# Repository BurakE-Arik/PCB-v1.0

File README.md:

# PCB Design v1.0 

## Description
This project is my first practical hardware work as a first-year Computer Engineering student. I developed it to learn hardware design processes, how to read schematics, and the standards used in PCB production.

---

## Visuals
For reviewers to quickly see the design, the front and back views of the board are shown below:

### PCB Front View

### PCB Back View

---

## Technical Details & Tools
Libraries and design rules (DRC) were used during the design process.

* **Design Tool:** Autodesk Eagle v9.6.2
* **Libraries:** * [SparkFun Electronics](https://github.com/sparkfun/SparkFun-Eagle-Libraries) (Connectors, LED, PowerSymbols, Resistors, Sensors, Switches)
    * [Custom Library](Design_Files/Custom_Library/) (Designed for specific componenets Arduiono Nano and LM 35)
* **Design Rules:** To minimize errors in the schematics, checks were performed using the [SparkFun DRU](Design_Files/DRU%20File/) files.

---

## Project Structure
The project folder is organized as follows:

* **[Design_Files](Design_Files):** Source Autodesk EAGLE schematic (.sch) and board (.brd) files.
* **[Gerber](Gerber):** Output files prepared for manufacturing in RS-274X format.
* **[Images](Images):** High-resolution design images.

---

## How to Use
1. `/Design_Files/Schemas` You can open the files in this folder using EAGLE or any compatible CAD software.
2. If you want to manufacture the board, you can directly send the `.zip` file in the `/Gerber` folder to a PCB manufacturer (such as JLCPCB, PCBWay, etc.).

---
**Author:** Burak Eslem Arık
**Contact:** [burakar1912@gmail.com](burakar1912@gmail.com), [Linkedin](https://www.linkedin.com/in/burak-eslem-arik-481045208/)

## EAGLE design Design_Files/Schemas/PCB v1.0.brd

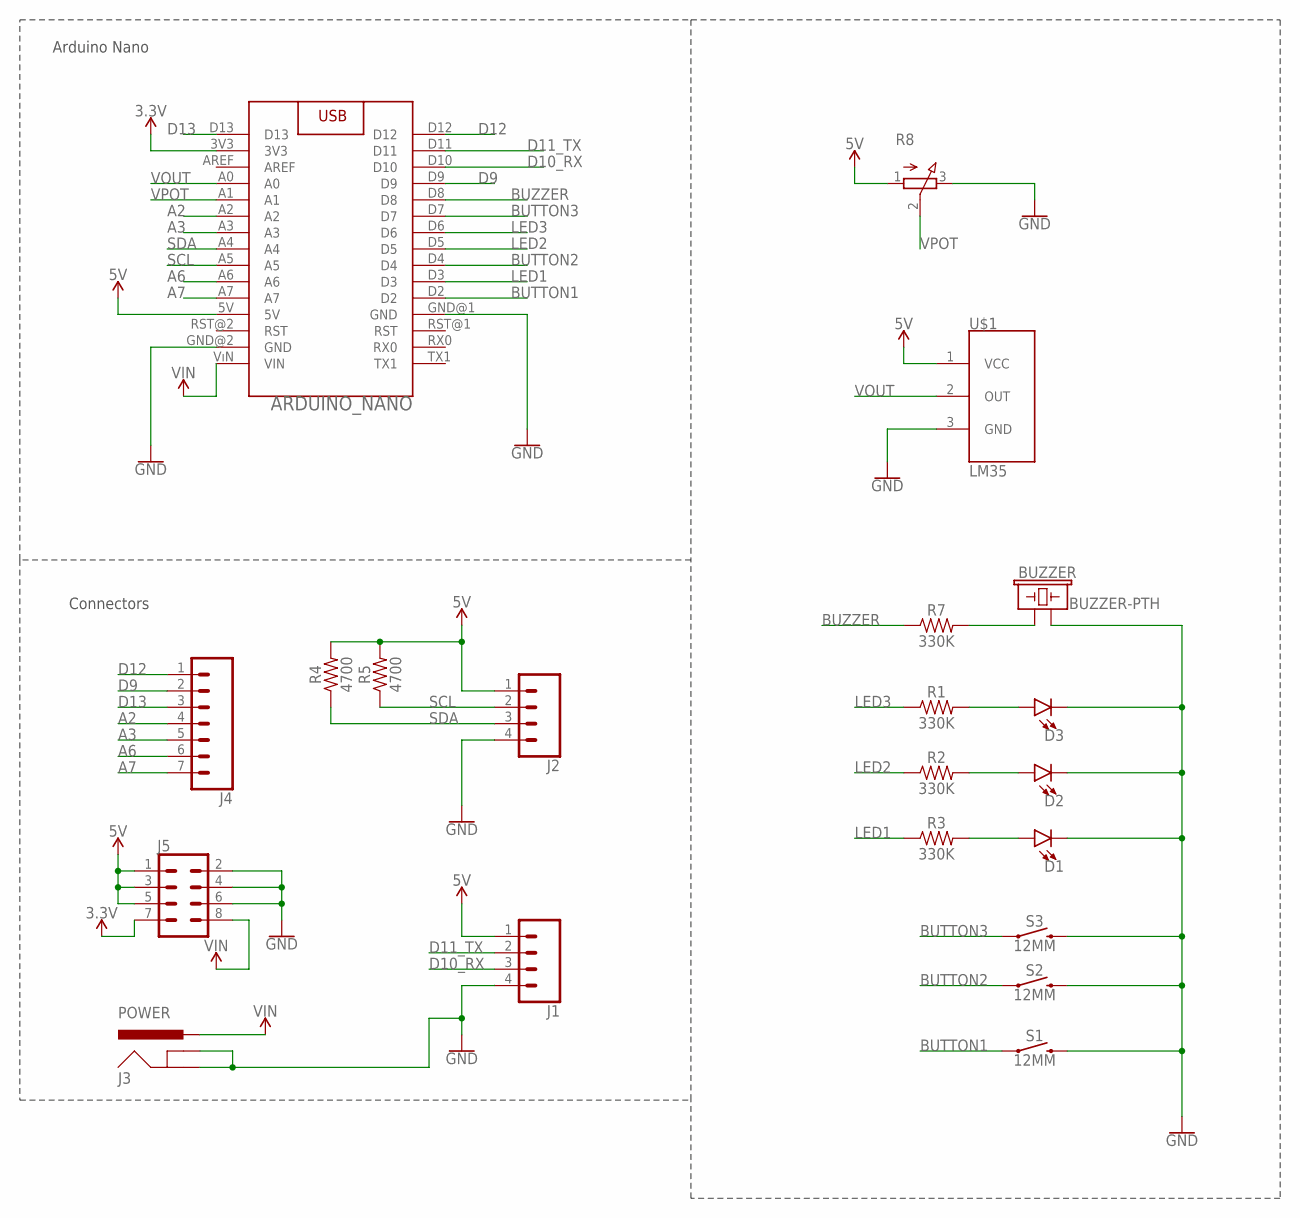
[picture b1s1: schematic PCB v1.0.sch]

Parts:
ARDUINO_NANO: ARDUINO_NANO
BUZZER: BUZZER-PTH; BUZZER-12MM
D1, D2, D3: LED-3MM-NO_SILK; LED_3MM-NS
J1, J2: CONN_04PTH; 1X04
J3: POWER; POWER_JACK_PTH
J4: CONN_07; 1X07
J5: CONN_04X2; 2X4
R1, R2, R3, R7: 330K; AXIAL-0.3
R4, R5: 4700; AXIAL-0.3
R8: 3RP/1610N
S1, S2, S3: 12MM; TACTILE_SWITCH_PTH_12MM
U$1: LM35; TO-92

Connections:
3.3V: ARDUINO_NANO.3V3, J5.7
5V: ARDUINO_NANO.5V, J1.1, J2.1, J5.1, J5.3, J5.5, R4.P$2 (2), R5.P$2 (2), R8.1 (A), U$1.1 (VCC)
A2: ARDUINO_NANO.A2, J4.4
A3: ARDUINO_NANO.A3, J4.5
A6: ARDUINO_NANO.A6, J4.6
A7: ARDUINO_NANO.A7, J4.7
BUTTON1: ARDUINO_NANO.D2, S1.1
BUTTON2: ARDUINO_NANO.D4, S2.1
BUTTON3: ARDUINO_NANO.D7, S3.1
BUZZER: ARDUINO_NANO.D8, R7.P$1 (1)
D9: ARDUINO_NANO.D9, J4.2
D10_RX: ARDUINO_NANO.D10, J1.3
D11_TX: ARDUINO_NANO.D11, J1.2
D12: ARDUINO_NANO.D12, J4.1
D13: ARDUINO_NANO.D13, J4.3
GND: ARDUINO_NANO.GND@1 (GND), ARDUINO_NANO.GND@2 (GND), BUZZER.- (2), D1.K (C), D2.K (C), D3.K (C), J1.4, J2.4, J3.GND, J3.GNDBREAK, J5.2, J5.4, J5.6, R8.3 (E), S1.3 (2), S2.3 (2), S3.3 (2), U$1.3 (GND)
LED1: ARDUINO_NANO.D3, R3.P$1 (1)
LED2: ARDUINO_NANO.D5, R2.P$1 (1)
LED3: ARDUINO_NANO.D6, R1.P$1 (1)
unnamed: BUZZER.+ (1), R7.P$2 (2)
unnamed: D3.A, R1.P$2 (2)
unnamed: D2.A, R2.P$2 (2)
unnamed: D1.A, R3.P$2 (2)
SCL: ARDUINO_NANO.A5, J2.2, R5.P$1 (1)
SDA: ARDUINO_NANO.A4, J2.3, R4.P$1 (1)
VIN: ARDUINO_NANO.VıN (VIN), J3.PWR, J5.8
VOUT: ARDUINO_NANO.A0, U$1.2 (OUT)
VPOT: ARDUINO_NANO.A1, R8.2 (S)

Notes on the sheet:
Arduino Nano
Connectors

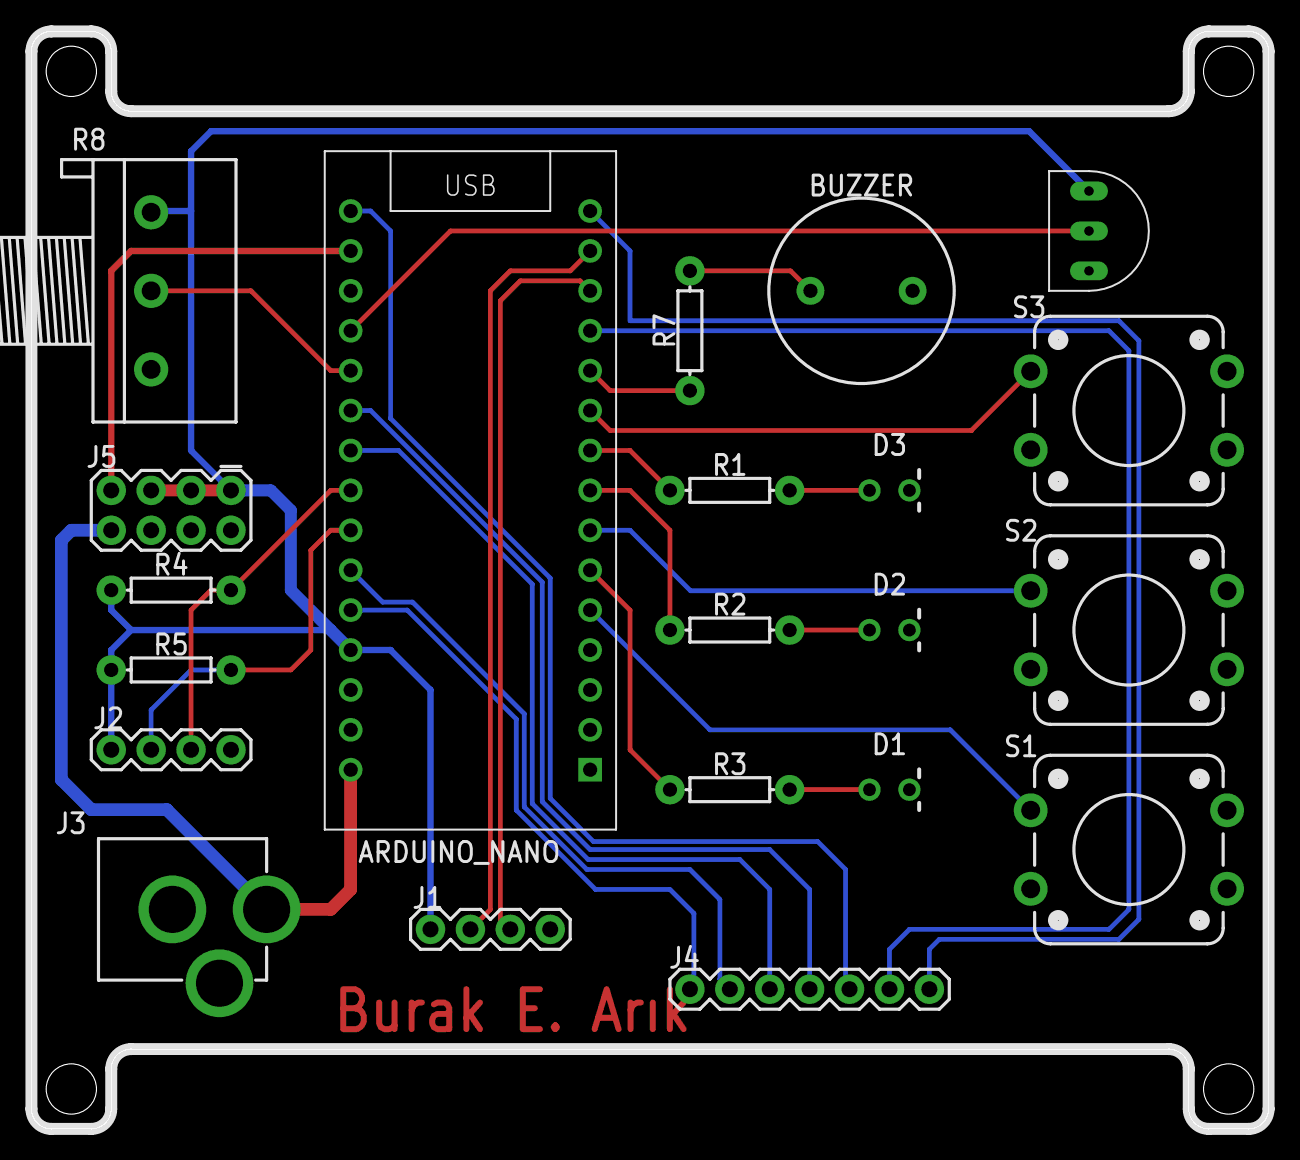
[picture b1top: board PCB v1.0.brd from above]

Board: 2 copper layers, 78.7 x 69.8 mm, 21 parts (0 on the bottom side), 28 nets.

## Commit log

2026-03-13 Initial Files
2026-03-13 README.md

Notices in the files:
parts and their libraries:
SparkFun-LED: Licensing: Creative Commons ShareAlike 4.0 International - https://creativecommons.org/licenses/by-sa/4.0
